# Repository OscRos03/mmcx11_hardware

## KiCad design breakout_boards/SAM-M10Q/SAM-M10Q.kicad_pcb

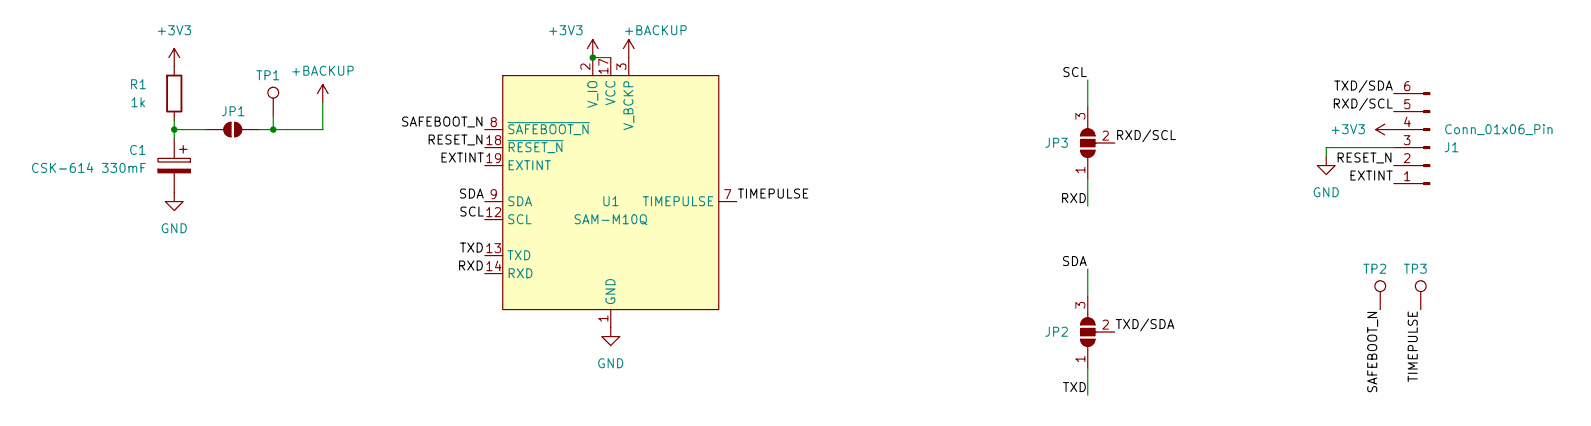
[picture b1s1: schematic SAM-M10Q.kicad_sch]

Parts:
C1: CSK-614 330mF; CP_CSK-334
J1: Conn_01x06_Pin; PinHeader_1x06_P2.54mm_Vertical_SMD_Pin1Left
JP1: SolderJumper_2_Open; SolderJumper-2_P1.3mm_Open_RoundedPad1.0x1.5mm
JP2, JP3: SolderJumper_3_Open; SolderJumper-3_P1.3mm_Open_RoundedPad1.0x1.5mm
R1: 1k; R_0603_1608Metric_Pad0.98x0.95mm_HandSolder
TP1, TP2, TP3: TestPoint; TestPoint_Pad_D1.5mm
U1: SAM-M10Q

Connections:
+3V3: J1.4, R1.2, U1.2 (V_IO), U1.17 (VCC)
+BACKUP: JP1.1 (A), TP1.1, U1.3 (V_BCKP)
/EXTINT: J1.1, U1.19 (EXTINT)
/RESET_N: J1.2, U1.18 (~RESET_N)
/RXD: JP3.1 (A), U1.14 (RXD)
/RXD/SCL: J1.5, JP3.2 (C)
/SAFEBOOT_N: TP2.1, U1.8 (~SAFEBOOT_N)
/SCL: JP3.3 (B), U1.12 (SCL)
/SDA: JP2.3 (B), U1.9 (SDA)
/TIMEPULSE: TP3.1, U1.7 (TIMEPULSE)
/TXD: JP2.1 (A), U1.13 (TXD)
/TXD/SDA: J1.6, JP2.2 (C)
GND: C1.2, J1.3, U1.1 (GND), U1.4 (GND), U1.5 (GND), U1.6 (GND), U1.10 (GND), U1.11 (GND), U1.15 (GND), U1.16 (GND), U1.20 (GND)
unnamed: C1.1, JP1.2 (B), R1.1

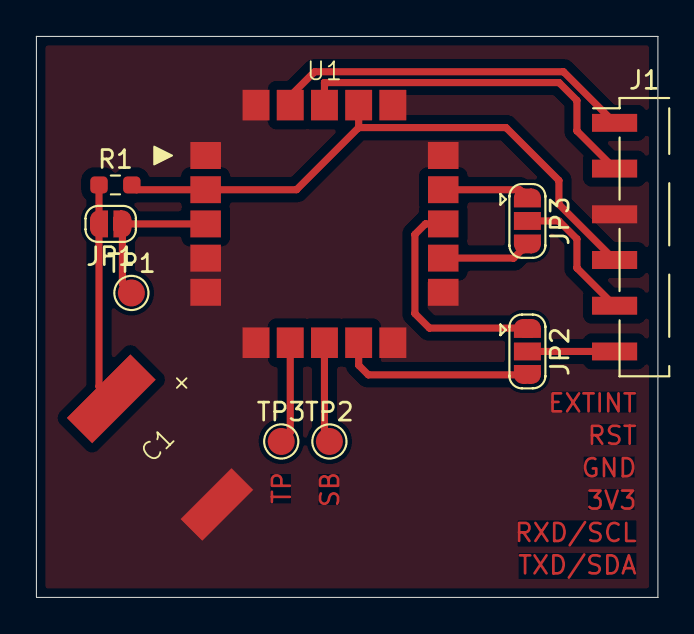
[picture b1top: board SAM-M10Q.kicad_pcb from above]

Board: 2 copper layers, 34.5 x 31.2 mm, 10 parts (0 on the bottom side), 14 nets.

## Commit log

2026-02-20 created libraries and breakout board for M10Q
2026-02-20 modified .gitignore and removed stuff that should not be included
2026-02-21 added things I forgor for last commit
2026-02-25 new symbol + some buses
2026-02-27 drew more busses and connections
2026-02-27 beginnings of power distribution maybe?
2026-03-03 moved stuff around
2026-03-06 moved files to their proper locations
2026-03-06 sx1262 reference design
2026-03-06 amended last commit
